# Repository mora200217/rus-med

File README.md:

# RUSMED
¡Conoce RUSMED! Una nueva herramienta para acelerar el proceso de diagnóstico de transtornos del manguito rotador 

---

## Sensores disponibles 
### IMU 
RUSMED cuenta con una unidad de medida inercial (IMU) BMI160. Publica la orientación del efector final. Esto permite una mayor escalabilidad del prototipo, al poder reconstruir el volumen analizado, a partir de la imagenes ultrasonográficas. 

### Integración con ROS2

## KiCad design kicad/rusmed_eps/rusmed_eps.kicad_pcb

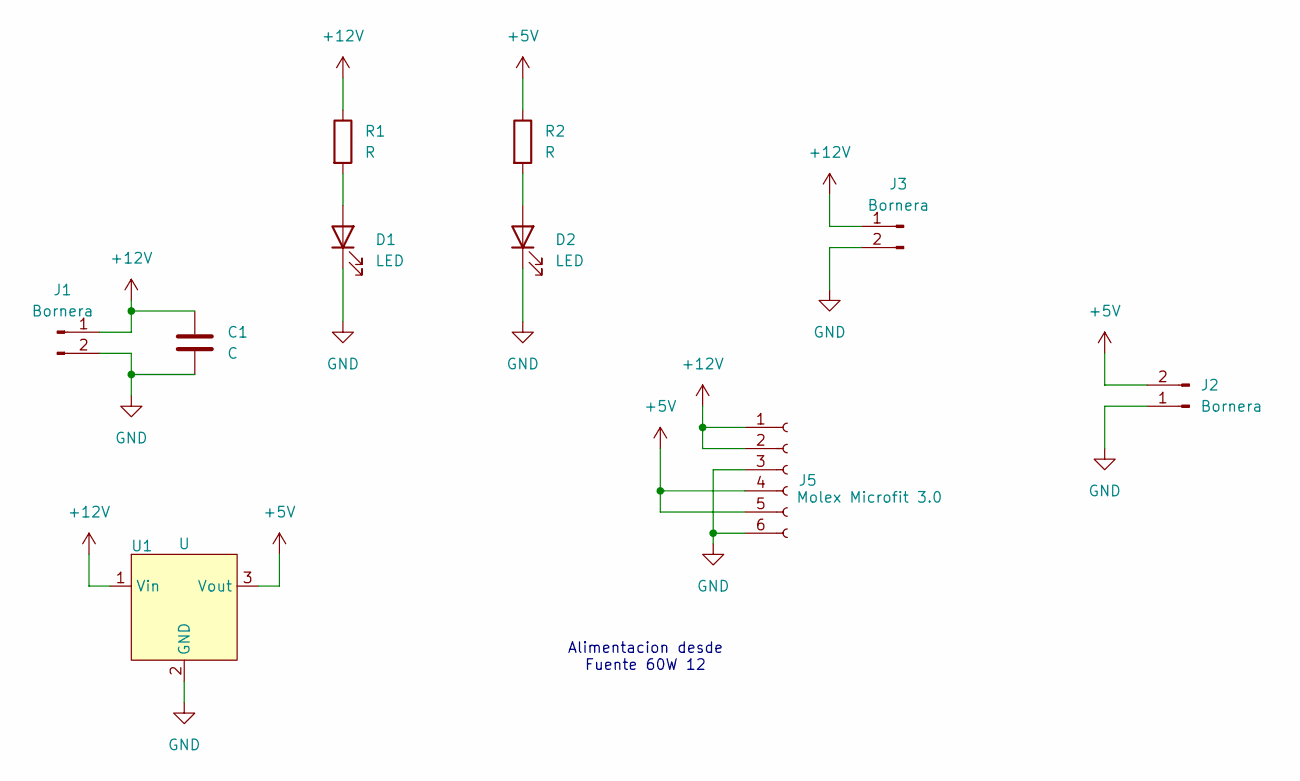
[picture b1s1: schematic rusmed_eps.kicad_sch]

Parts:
C1: C; C_Radial_D10.0mm_H16.0mm_P5.00mm
D1, D2: LED; LED_D5.0mm
J1, J2, J3: Bornera; TerminalBlock_Phoenix_MKDS-1,5-2_1x02_P5.00mm_Horizontal
J5: Molex Microfit 3.0; Molex_Micro-Fit_3.0_43045-0612_2x03_P3.00mm_Vertical
R1, R2: R; R_Axial_DIN0207_L6.3mm_D2.5mm_P10.16mm_Horizontal
U1: U; hw_0468

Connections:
+5V: J2.2, J5.4, J5.5, R2.1, U1.3 (Vout)
+12V: C1.1, J1.1, J3.1, J5.1, J5.2, R1.1, U1.1 (Vin)
GND: C1.2, D1.1 (K), D2.1 (K), J1.2, J2.1, J3.2, J5.3, J5.6, U1.2 (GND)
unnamed: D1.2 (A), R1.2
unnamed: D2.2 (A), R2.2

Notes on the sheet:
Alimentacion desde Fuente 60W 12

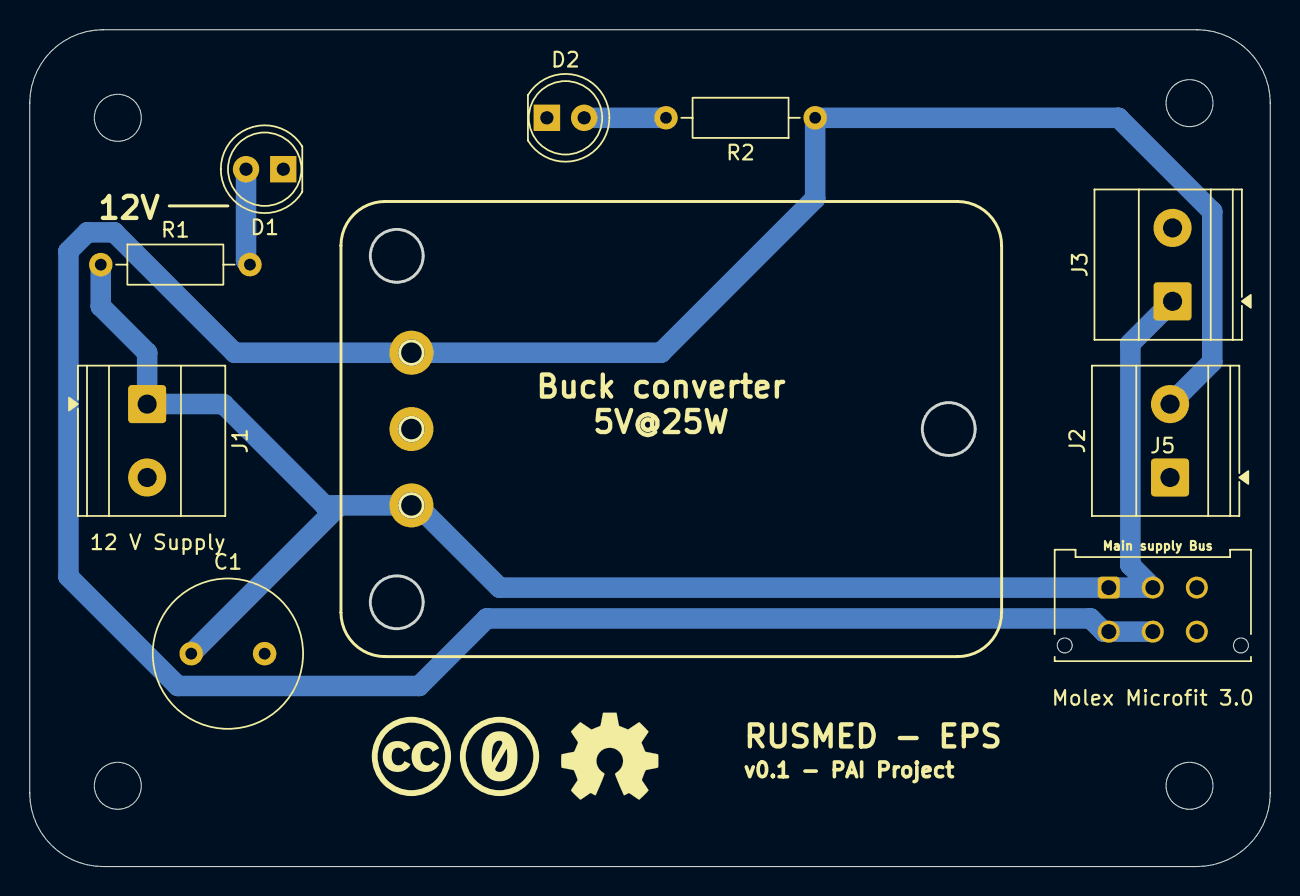
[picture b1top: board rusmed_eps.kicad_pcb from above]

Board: 2 copper layers, 84.4 x 56.9 mm, 14 parts (0 on the bottom side), 5 nets.

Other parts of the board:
M1, M2, M3, M4: MountingHole_3.2mm_M3

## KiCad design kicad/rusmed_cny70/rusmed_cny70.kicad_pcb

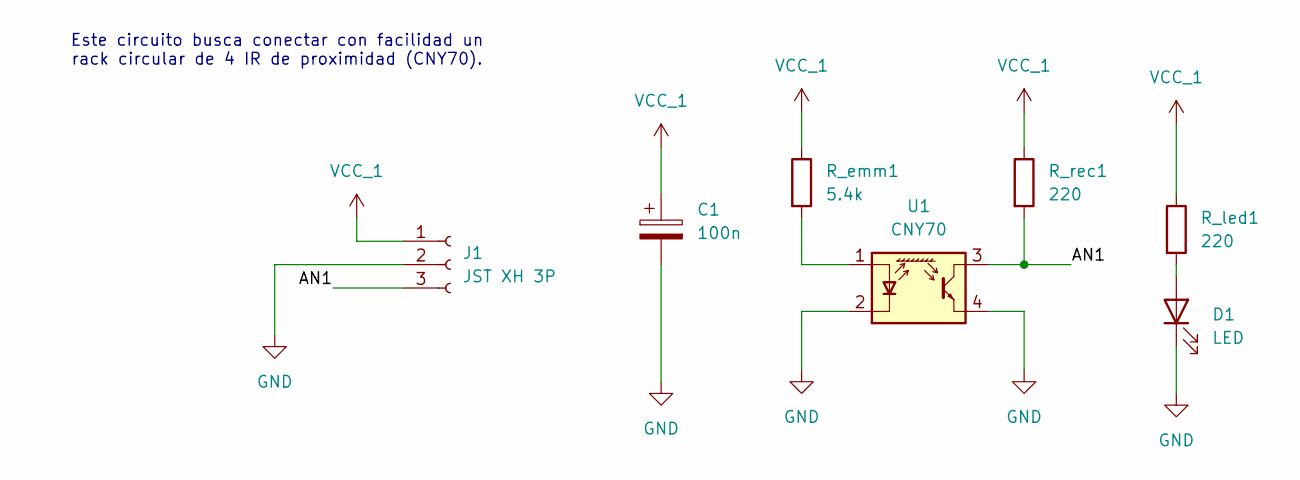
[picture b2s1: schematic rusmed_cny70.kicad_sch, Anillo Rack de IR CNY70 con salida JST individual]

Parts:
C1: 100n; CP_Elec_6.3x4.9
D1: LED; LED_1210_3225Metric_Pad1.42x2.65mm_HandSolder
J1: JST XH 3P; JST_XH_B3B-XH-A_1x03_P2.50mm_Vertical
R_emm1: 5.4k; R_1206_3216Metric
R_led1: 220; R_1206_3216Metric
R_rec1: 220; R_1206_3216Metric
U1: CNY70; Vishay_CNY70

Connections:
/AN1: J1.3, R_rec1.2, U1.3 (C)
GND: C1.2, D1.1 (K), J1.2, U1.2 (K), U1.4 (E)
unnamed: D1.2 (A), R_led1.2
unnamed: R_emm1.2, U1.1 (A)
VCC_1: C1.1, J1.1, R_emm1.1, R_led1.1, R_rec1.1

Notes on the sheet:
Este circuito busca conectar con facilidad un rack circular de 4 IR de proximidad (CNY70).

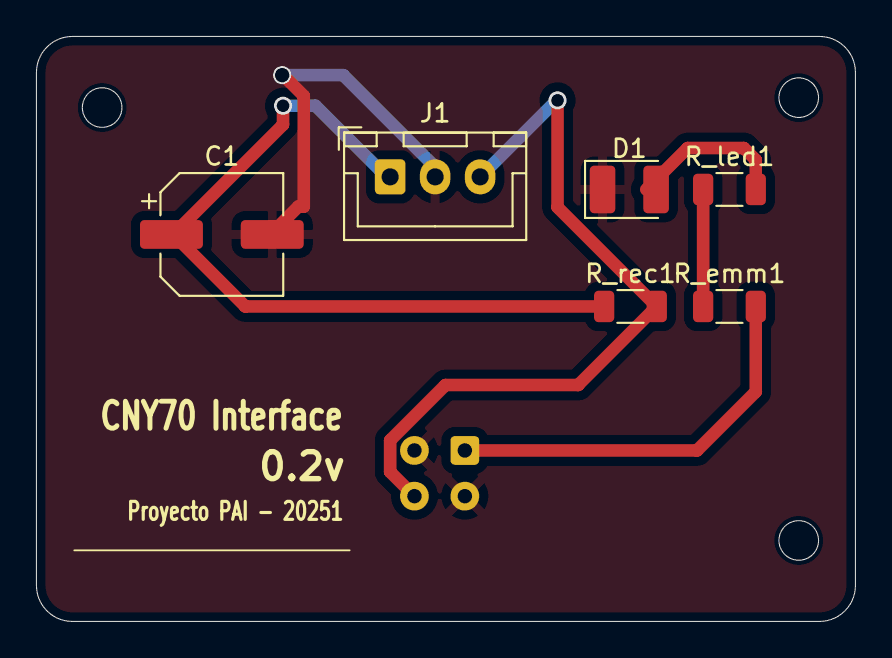
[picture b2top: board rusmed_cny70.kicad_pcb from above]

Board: 2 copper layers, 45.5 x 32.5 mm, 7 parts (1 on the bottom side), 5 nets.

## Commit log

2025-06-05 [Update] main
2025-06-05 [Update]
2025-06-05 [Update] Proteccion de polaridad
2025-06-27 [New] MplabX project. Agregado proyecto de prueba de I2C para PIC16F1827. Protocolo creado y configurado periferico (PIC) como esclavo. Se hace la prueba con arduino satisfactoriamente. No tiene lazo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
2025-06-27 [Update] Control Law Simscape modelado de lazo de control axial.
2025-06-30 [New] Images for archive. Rusmed pcb design
2025-06-30 [Update] Added gitignore files
2025-06-30 [New] Mplab files. I2C added for PIC16F1827. Basic encoder conter added. Basic Pulse Important to notice that the tests for the PIC to control the stepper, is with a LED. Just noticing if it can be u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
2025-06-30 [New] RUSMED cny70 pcb. With Schematic
2025-06-30 [New] Simulink simulation for control loop in axial joint.
    It takes the basic model of a DC motor an a first approx to the close loop model. It need to me updated
    with the real DC motor properties. The encoder model (discrete) works without direction
2025-06-30 [Delete] DS_store clean
2025-06-30 [New] rusmed_eps system. Basic connectors added. No HW-468. Pending
2025-07-01 [New] Submodules. Django GUI
2025-07-02 [Update] change in rusmed_axial_joint_controller. Refactor
2025-07-02 [Update] Change format. Organize info in mplabx and clean project. More readable structure.
    It still works in this manner:
    - PIC sends angle position from encoder in Little Endian from ros2control HW interface (Broadcaster)
    - Waits for a command (If 0x02 it moves the DC motor left. And 0x03 Right)
2025-07-06 [Update] test
2025-07-06 [Update] test code in arduino for DRV8825
2025-07-06 [New] Drawio base for diagrams of the project
2025-07-06 Create img
2025-07-06 Create img_verificacion
2025-07-06 Create img_R_y_E
2025-07-06 Create img_DC
2025-07-06 Create img_R
2025-07-06 Create img_DM
2025-07-06 Create img_D
2025-07-06 Create img_P
2025-07-07 [Update] Drawios temp files ignores
2025-07-07 [New] Docker compose information
